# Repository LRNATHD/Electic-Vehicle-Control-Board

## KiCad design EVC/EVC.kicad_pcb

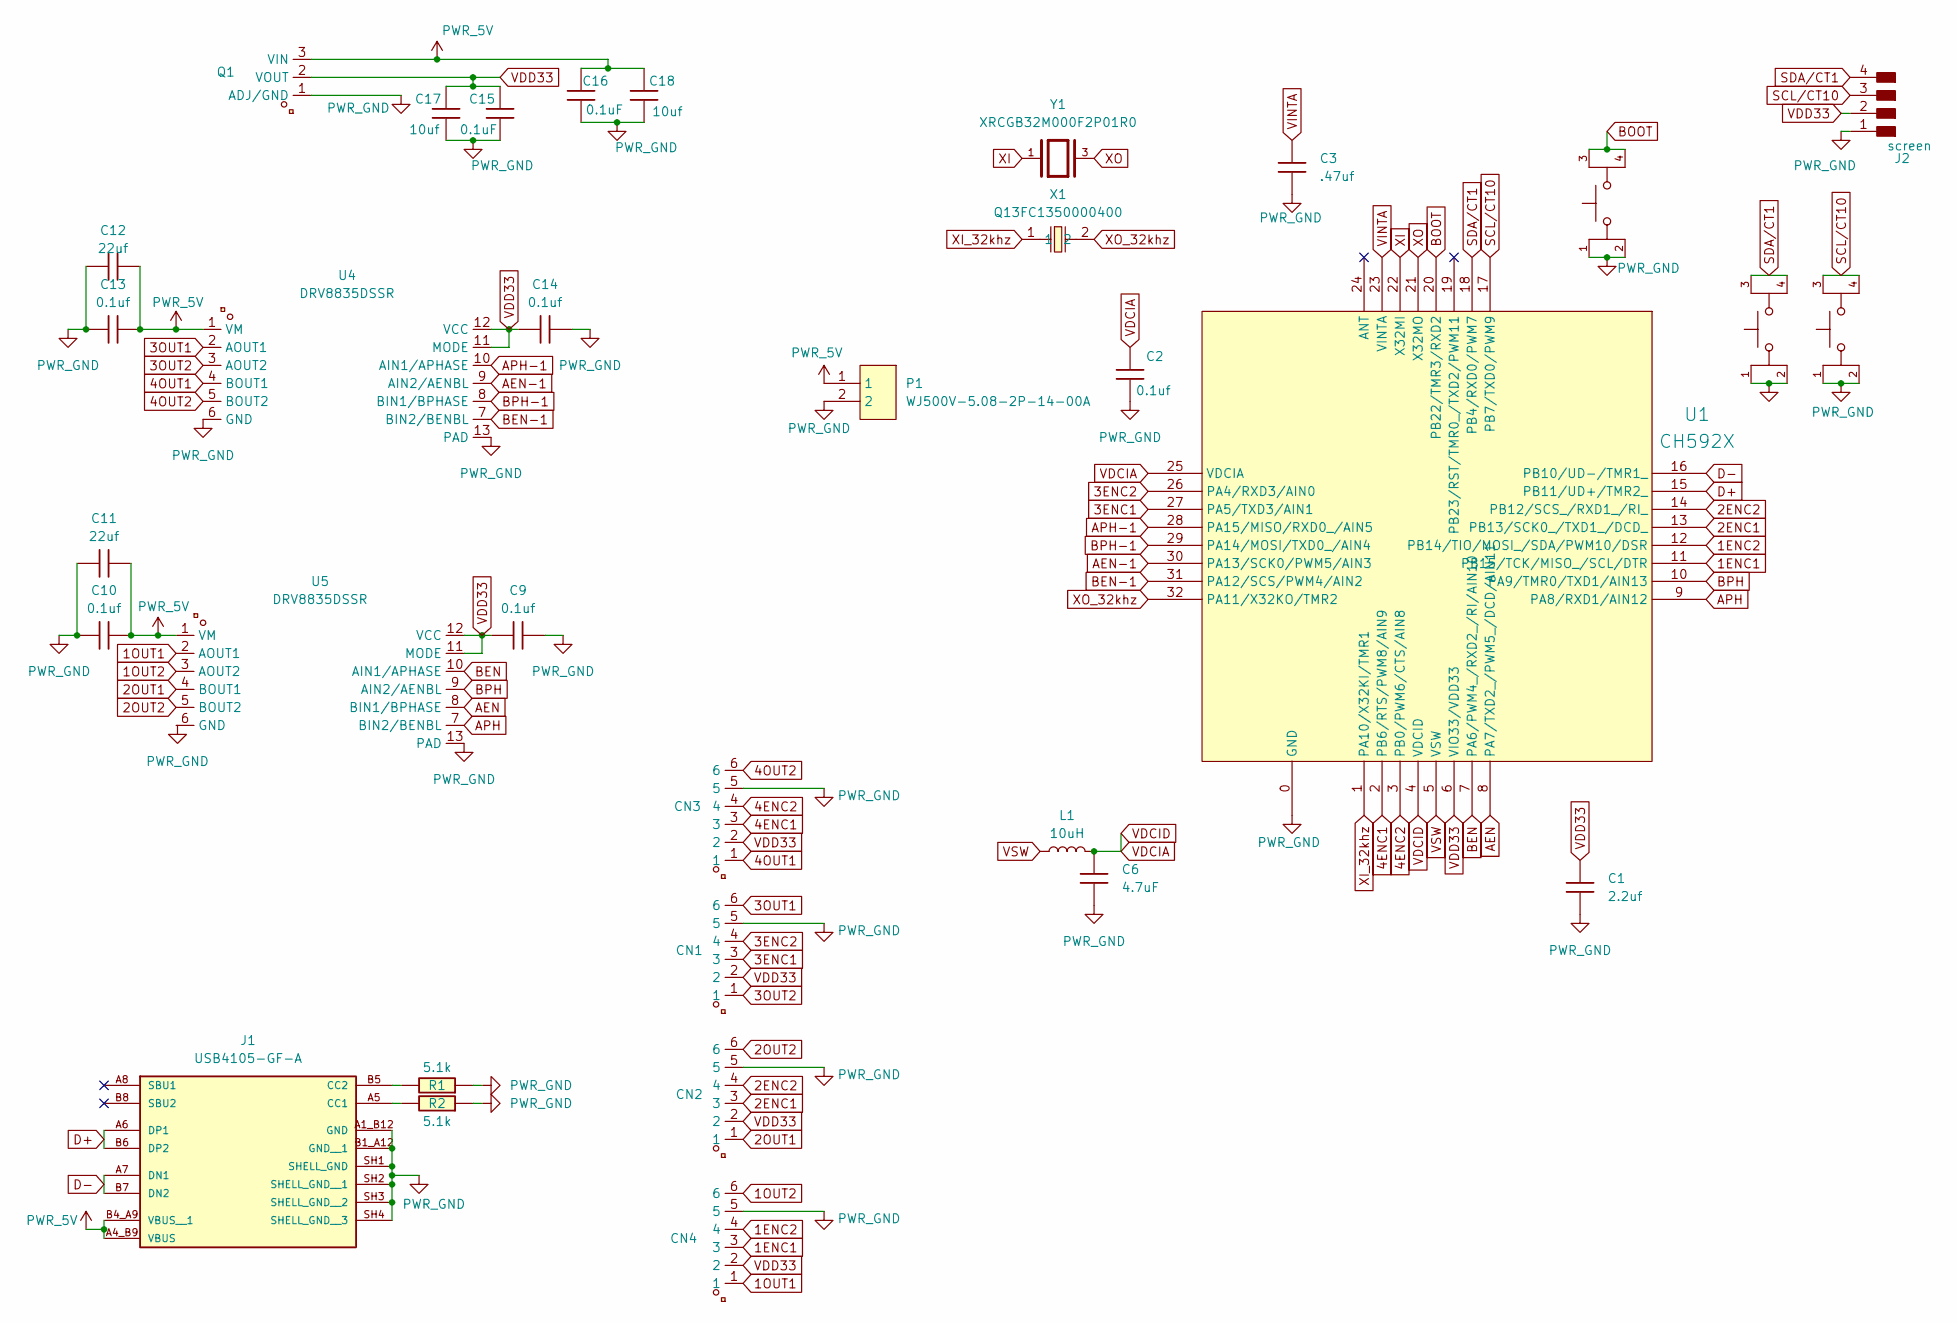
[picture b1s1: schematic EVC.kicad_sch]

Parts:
C1: 2.2uf; C_0603
C2, C9, C10, C13, C14: 0.1uf; C_0603
C3: .47uf; C_0603
C6: 4.7uF; C_0603
C11, C12: 22uf; C_1206
C15, C16: 0.1uF; C_0603
C17, C18: 10uf; C_0603
CN1, CN2, CN3, CN4: HC-ZH1.5-6AW; CONN-TH_6P-P1.50_HCTL_C-ZH1.5-6AW; LCSC Part C2845569
J1: USB4105-GF-A; usbc; PARTREV B4
J2: screen; PinHeader_01x04_P2.54mm_Vertical_THT_D1mm
L1: 10uH; 0603
P1: WJ500V-5.08-2P-14-00A; CONN-TH_2P-P5.00_WJ500V-5.08-2P; LCSC Part C8465
Q1: AMS1117-3.3V_C5120796; SOT-89-3_L4.5-W2.5-P1.50-LS4.2-BR; LCSC Part C5120796
R1, R2: 5.1k; 0603
S1, S2, S3: TL3365AF180QG; button; PARTREV A
U1: CH592X; QFN32_4X4
U4, U5: DRV8835DSSR; WSON-12_L3.0-W2.0-P0.50-BL-EP; LCSC Part C129328
X1: Q13FC1350000400; FC-135R_L3.2-W1.5; LCSC Part C32346
Y1: XRCGB32M000F2P01R0; 32mhz crystal; PARTREV N/A

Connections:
1ENC1: CN4.3, U1.11 (PB15/TCK/MISO_/SCL/DTR)
1ENC2: CN4.4, U1.12 (PB14/TIO/MOSI_/SDA/PWM10/DSR)
1OUT1: CN4.1, U5.2 (AOUT1)
1OUT2: CN4.6, U5.3 (AOUT2)
2ENC1: CN2.3, U1.13 (PB13/SCK0_/TXD1_/DCD_)
2ENC2: CN2.4, U1.14 (PB12/SCS_/RXD1_/RI_)
2OUT1: CN2.1, U5.4 (BOUT1)
2OUT2: CN2.6, U5.5 (BOUT2)
3ENC1: CN1.3, U1.27 (PA5/TXD3/AIN1)
3ENC2: CN1.4, U1.26 (PA4/RXD3/AIN0)
3OUT1: CN1.6, U4.2 (AOUT1)
3OUT2: CN1.1, U4.3 (AOUT2)
4ENC1: CN3.3, U1.2 (PB6/RTS/PWM8/AIN9)
4ENC2: CN3.4, U1.3 (PB0/PWM6/CTS/AIN8)
4OUT1: CN3.1, U4.4 (BOUT1)
4OUT2: CN3.6, U4.5 (BOUT2)
AEN: U1.8 (PA7/TXD2_/PWM5_/DCD/AIN11), U5.8 (BIN1/BPHASE)
AEN-1: U1.30 (PA13/SCK0/PWM5/AIN3), U4.9 (AIN2/AENBL)
APH: U1.9 (PA8/RXD1/AIN12), U5.7 (BIN2/BENBL)
APH-1: U1.28 (PA15/MISO/RXD0_/AIN5), U4.10 (AIN1/APHASE)
BEN: U1.7 (PA6/PWM4_/RXD2_/RI/AIN10), U5.10 (AIN1/APHASE)
BEN-1: U1.31 (PA12/SCS/PWM4/AIN2), U4.7 (BIN2/BENBL)
BOOT: S2.3, S2.4, U1.20 (PB22/TMR3/RXD2)
BPH: U1.10 (PA9/TMR0/TXD1/AIN13), U5.9 (AIN2/AENBL)
BPH-1: U1.29 (PA14/MOSI/TXD0_/AIN4), U4.8 (BIN1/BPHASE)
D+: J1.A6 (DP1), J1.B6 (DP2), U1.15 (PB11/UD+/TMR2_)
D-: J1.A7 (DN1), J1.B7 (DN2), U1.16 (PB10/UD-/TMR1_)
unnamed: J1.A5 (CC1), R2.1
unnamed: J1.B5 (CC2), R1.1
PWR_5V: C10.2, C11.2, C12.2, C13.2, C16.2, C18.2, J1.A4_B9 (VBUS), J1.B4_A9 (VBUS__1), P1.1, Q1.3 (VIN), U4.1 (VM), U5.1 (VM)
PWR_GND: C1.2, C2.1, C3.1, C6.2, C9.2, C10.1, C11.1, C12.1, C13.1, C14.2, C15.1, C16.1, C17.1, C18.1, CN1.5, CN2.5, CN3.5, CN4.5, J1.A1_B12 (GND), J1.B1_A12 (GND__1), J1.SH1 (SHELL_GND), J1.SH2 (SHELL_GND__1), J1.SH3 (SHELL_GND__2), J1.SH4 (SHELL_GND__3), J2.1, P1.2, Q1.1 (ADJ/GND), R1.2, R2.2, S1.1, S1.2, S2.1, S2.2, S3.1, S3.2, U1.0 (GND), U4.6 (GND), U4.13 (PAD), U5.13 (PAD)
SCL/CT10: J2.3, S3.3, S3.4, U1.17 (PB7/TXD0/PWM9)
SDA/CT1: J2.4, S1.3, S1.4, U1.18 (PB4/RXD0/PWM7)
VDCIA: C2.2, C6.1, L1.2, U1.4 (VDCID), U1.25 (VDCIA)
VDD33: C1.1, C9.1, C14.1, C15.2, C17.2, CN1.2, CN2.2, CN3.2, CN4.2, J2.2, Q1.2 (VOUT), U1.6 (VIO33/VDD33), U4.11 (MODE), U4.12 (VCC), U5.11 (MODE), U5.12 (VCC)
VINTA: C3.2, U1.23 (VINTA)
VSW: L1.1, U1.5 (VSW)
XI: U1.22 (X32MI), Y1.1
XI_32khz: U1.1 (PA10/X32KI/TMR1), X1.1
XO: U1.21 (X32MO), Y1.3
XO_32khz: U1.32 (PA11/X32KO/TMR2), X1.2

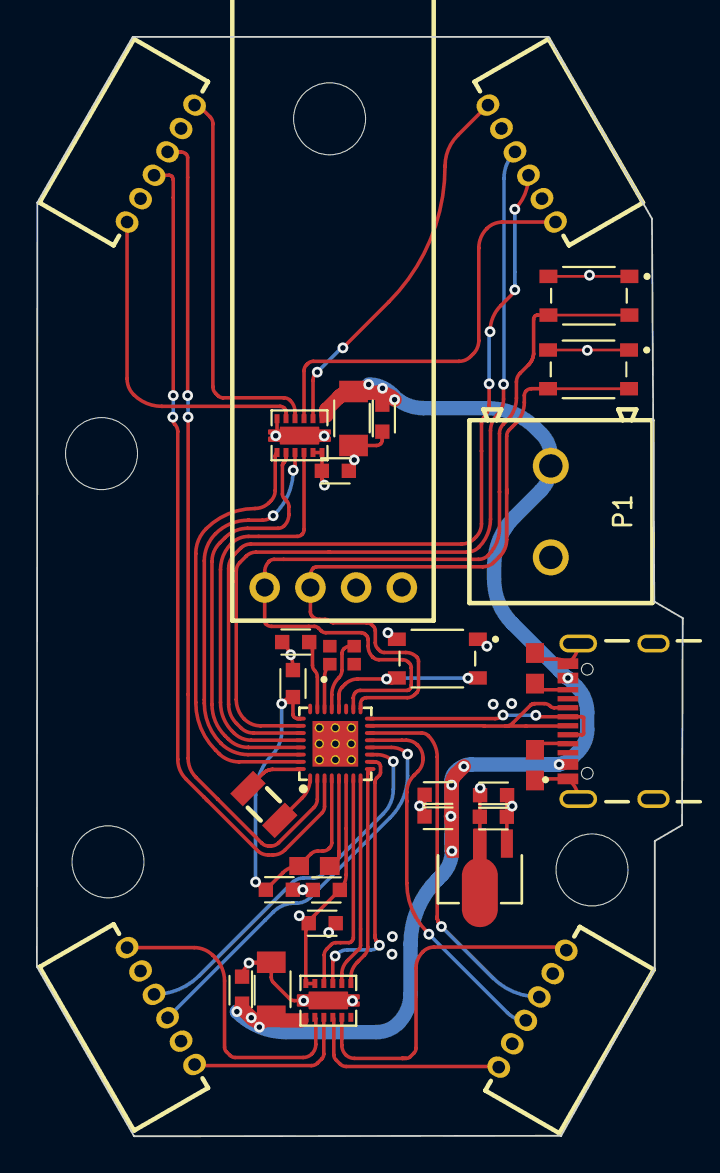
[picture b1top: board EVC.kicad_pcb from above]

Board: 4 copper layers, 35.9 x 61.1 mm, 33 parts (1 on the bottom side), 41 nets.

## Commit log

2025-12-01 I misspelled the repos name!?!?!?
2025-12-02 started work, prolly gonna use the ch592x since thats the next step form ch572
2025-12-03 started work on layout, design nearly done, need to order components soon...
2025-12-05 done
2026-01-01 fixed that one connector + flipped screw terminal
2026-01-20 fixed some stuff reorder should be aokay
2026-01-20 forgot to save it dont trust the last one
